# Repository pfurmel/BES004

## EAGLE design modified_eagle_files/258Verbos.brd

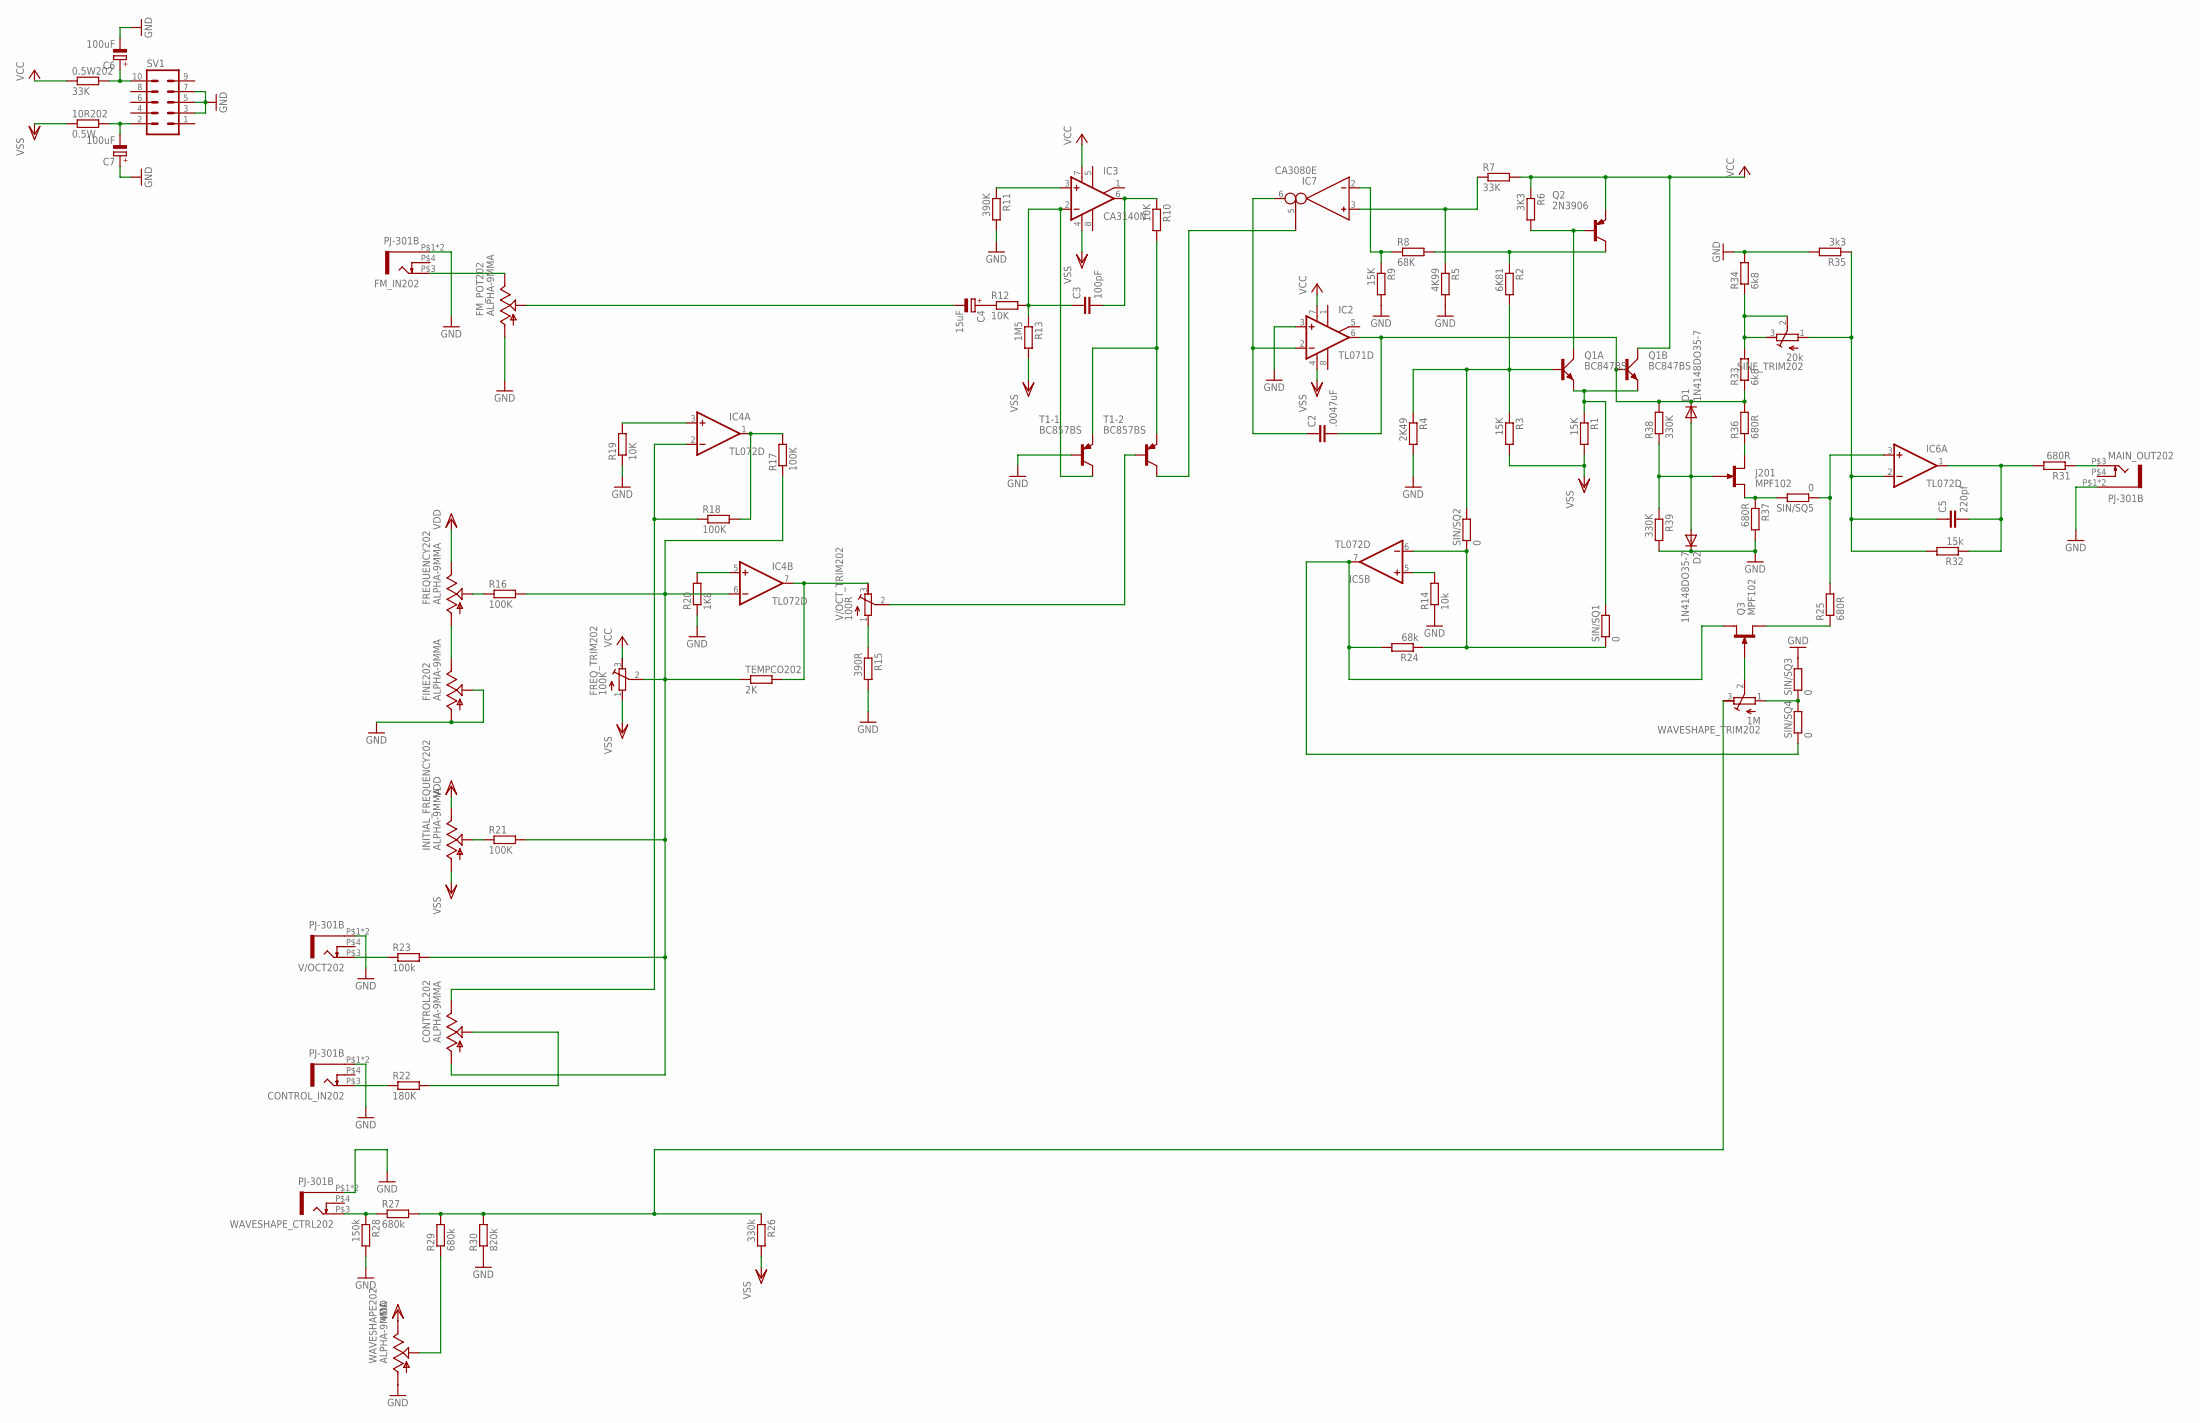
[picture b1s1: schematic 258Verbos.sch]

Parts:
0.5W202: 33K; R0805
10R202: 0.5W; R0805
C2: .0047uF; C5B4.5
C3: 100pF; C2.5-3
C4: 15uF; E2,5-6E
C5: 220pf; C2.5-3
C6, C7: 100uF; E2,5-6E
CONTROL202: ALPHA-9MMA; EVUF
CONTROL_IN202: PJ-301B
D1, D2: 1N4148DO35-7; DO35-7
FINE202: ALPHA-9MMA; EVUF
FM_IN202: PJ-301B
FM_POT202: ALPHA-9MMA; EVUF
FREQUENCY202: ALPHA-9MMA; EVUF
FREQ_TRIM202: 100K; RTRIM64W
IC2: TL071D; SO08
IC3: CA3140N; DIL08
IC4, IC5, IC6: TL072D; SO08
IC7: CA3080E; DIL08
INITIAL_FREQUENCY202: ALPHA-9MMA; EVUF
J201: MPF102; TO92F
MAIN_OUT202: PJ-301B
Q1: BC847BS; SOT363_PHILIPS
Q2: 2N3906; TO92
Q3: MPF102; TO92F
R1, R3, R9: 15K; R0805
R2: 6K81; R0805
R4: 2K49; R0805
R5: 4K99; R0805
R6: 3K3; R0805
R7: 33K; R0805
R8: 68K; R0805
R10, R12, R19: 10K; R0805
R11: 390K; R0805
R13: 1M5; R0805
R14: 10k; R0805
R15: 390R; R0805
R16, R17, R18, R21: 100K; R0805
R20: 1K8; R0805
R22: 180K; R0805
R23: 100k; R0805
R24: 68k; R0805
R25, R31, R36, R37: 680R; R0805
R26: 330k; R0805
R27, R29: 680k; R0805
R28: 150k; R0805
R30: 820k; R0805
R32: 15k; R0805
R33, R34: 6k8; R0805
R35: 3k3; R0805
R38, R39: 330K; R0805
SIN/SQ1, SIN/SQ2, SIN/SQ3, SIN/SQ4, SIN/SQ5: 0; R0805
SINE_TRIM202: 20k; RTRIM64W
SV1: 10_PIN_HEADER; MA05-2
T1: BC857BS; SOT363
TEMPCO202: 2K; R0805
V/OCT202: PJ-301B
V/OCT_TRIM202: 100R; RTRIM64W
WAVESHAPE202: ALPHA-9MMA; EVUF
WAVESHAPE_CTRL202: PJ-301B
WAVESHAPE_TRIM202: 1M; RTRIM64W

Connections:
GND: C6.-, C7.+, CONTROL_IN202.P$1 (5), CONTROL_IN202.P$2 (5), D2.C, FINE202.1 (A), FINE202.2 (S), FM_IN202.P$1 (5), FM_IN202.P$2 (5), FM_POT202.1 (A), IC2.3 (+IN), MAIN_OUT202.P$1 (5), MAIN_OUT202.P$2 (5), R4.2, R5.2, R9.2, R11.2, R14.1, R15.2, R19.1, R20.1, R28.2, R30.1, R34.2, R35.2, R37.2, R39.2, SIN/SQ3.2, SV1.3, SV1.5, SV1.7, T1.2 (B), V/OCT202.P$1 (5), V/OCT202.P$2 (5), WAVESHAPE202.1 (A), WAVESHAPE_CTRL202.P$1 (5), WAVESHAPE_CTRL202.P$2 (5)
unnamed: Q1.1 (E), Q1.4 (E), R1.1, SIN/SQ1.2
unnamed: Q1.6 (C), Q2.2 (B), R6.2
unnamed: Q2.1 (C), R2.1, R8.2
unnamed: Q1.2 (B), R2.2, R3.1, R4.1, SIN/SQ2.2
unnamed: J201.1 (D), R36.1
unnamed: C2.1, IC2.2 (-IN), IC7.6 (OUT)
unnamed: IC7.3 (IN_P), R5.1, R7.1
unnamed: IC7.2 (IN_N), R8.1, R9.1
unnamed: R10.2, T1.1 (E), T1.4 (E)
unnamed: C3.2, IC3.6 (OUT), R10.1
unnamed: C3.1, IC3.2 (-IN), R12.2, R13.1, T1.6 (C)
unnamed: IC3.3 (+IN), R11.1
unnamed: C4.+, R12.1
unnamed: T1.5 (B), V/OCT_TRIM202.2 (S)
unnamed: R15.1, V/OCT_TRIM202.1 (A)
unnamed: IC4.7 (OUT), TEMPCO202.2, V/OCT_TRIM202.3 (E)
unnamed: CONTROL202.1 (A), FREQ_TRIM202.2 (S), IC4.6 (-IN), R16.2, R17.1, R21.2, R23.2, TEMPCO202.1
unnamed: IC4.1 (OUT), R17.2, R18.2
unnamed: CONTROL202.3 (E), IC4.2 (-IN), R18.1
unnamed: IC4.3 (+IN), R19.2
unnamed: IC4.5 (+IN), R20.2
unnamed: C4.-, FM_POT202.2 (S)
unnamed: FREQUENCY202.2 (S), R16.1
unnamed: IC7.5 (I_BIAS), T1.3 (C)
unnamed: INITIAL_FREQUENCY202.2 (S), R21.1
unnamed: FM_IN202.P$3 (3), FM_POT202.3 (E)
unnamed: CONTROL_IN202.P$3 (3), R22.1
unnamed: CONTROL202.2 (S), R22.2
unnamed: R23.1, V/OCT202.P$3 (3)
unnamed: IC5.5 (+IN), R14.2
unnamed: IC5.6 (-IN), R24.1, SIN/SQ1.1, SIN/SQ2.1
unnamed: IC5.7 (OUT), Q3.1 (D), R24.2, SIN/SQ4.1
unnamed: C5.2, IC6.1 (OUT), R31.2, R32.1
unnamed: Q3.2 (S), R25.1
unnamed: IC6.3 (+IN), R25.2, SIN/SQ5.1
unnamed: Q3.3 (G), WAVESHAPE_TRIM202.2 (S)
unnamed: SIN/SQ3.1, SIN/SQ4.2, WAVESHAPE_TRIM202.1 (A)
unnamed: R27.1, R28.1, WAVESHAPE_CTRL202.P$3 (3)
unnamed: R26.1, R27.2, R29.2, R30.2, WAVESHAPE_TRIM202.3 (E)
unnamed: R29.1, WAVESHAPE202.2 (S)
unnamed: MAIN_OUT202.P$3 (3), R31.1
unnamed: C5.1, IC6.2 (-IN), R32.2, R35.1, SINE_TRIM202.1 (A)
unnamed: R33.2, R34.1, SINE_TRIM202.2 (S), SINE_TRIM202.3 (E)
unnamed: D1.A, D2.A, J201.3 (G), R38.1, R39.1
unnamed: C2.2, D1.C, IC2.6 (OUT), Q1.5 (B), R33.1, R36.2, R38.2
unnamed: J201.2 (S), R37.1, SIN/SQ5.2
unnamed: 0.5W202.2, C6.+, SV1.10
unnamed: 10R202.2, C7.-, SV1.2
unnamed: FINE202.3 (E), FREQUENCY202.1 (A)
V+: IC4.8 (V+), IC5.8 (V+), IC6.8 (V+)
V-: IC4.4 (V-), IC5.4 (V-), IC6.4 (V-)
VCC: 0.5W202.1, FREQ_TRIM202.3 (E), IC2.7 (V+), IC3.7 (V+), Q1.3 (C), Q2.3 (E), R6.1, R7.2
VDD: FREQUENCY202.3 (E), INITIAL_FREQUENCY202.3 (E), WAVESHAPE202.3 (E)
VSS: 10R202.1, FREQ_TRIM202.1 (A), IC2.4 (V-), IC3.4 (V-), INITIAL_FREQUENCY202.1 (A), R1.2, R3.2, R13.2, R26.2

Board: 2 copper layers, 82 parts (11 on the bottom side), 55 nets, no tracks yet.

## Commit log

2018-02-06 Modified footprint for pots. Changed silkscreen text. Rerouted
